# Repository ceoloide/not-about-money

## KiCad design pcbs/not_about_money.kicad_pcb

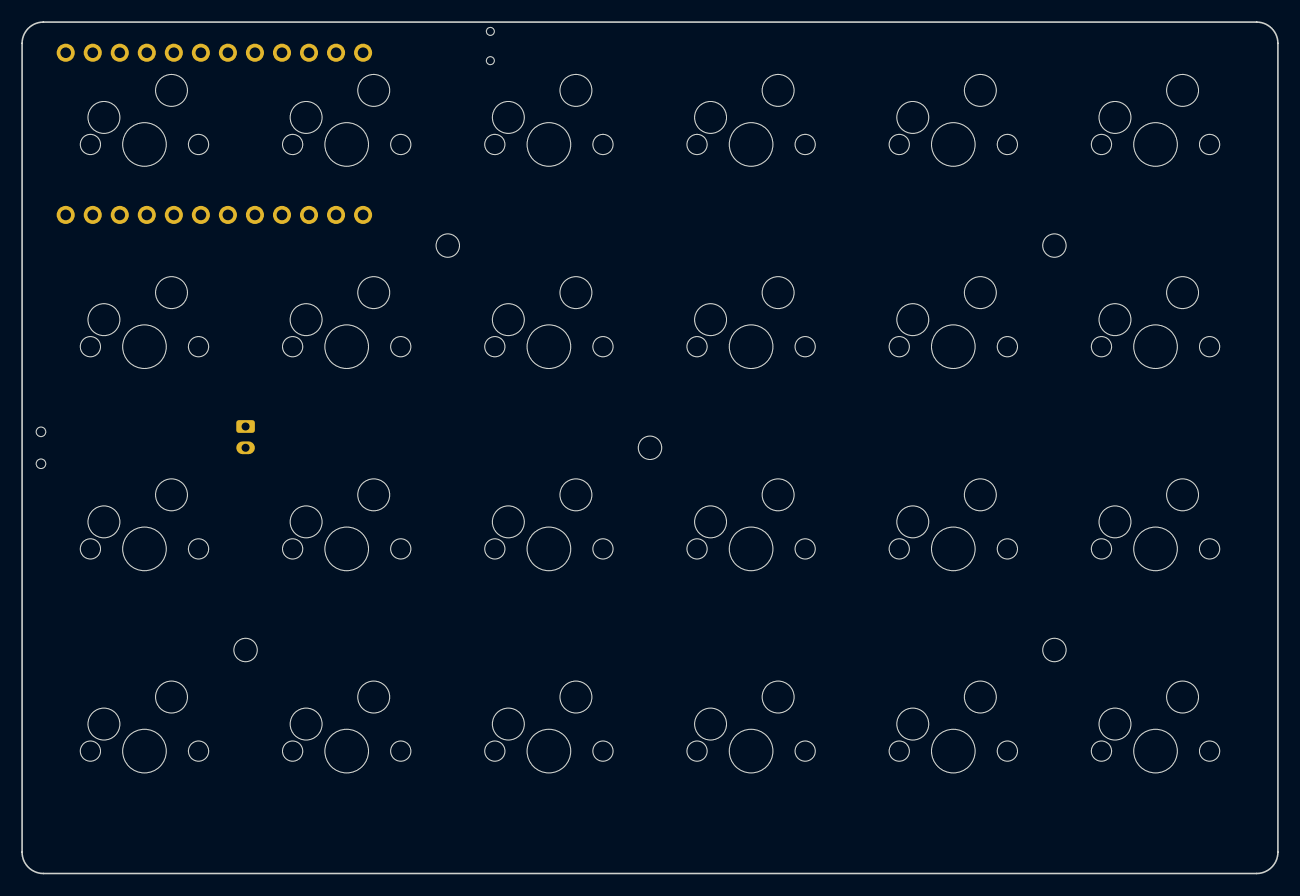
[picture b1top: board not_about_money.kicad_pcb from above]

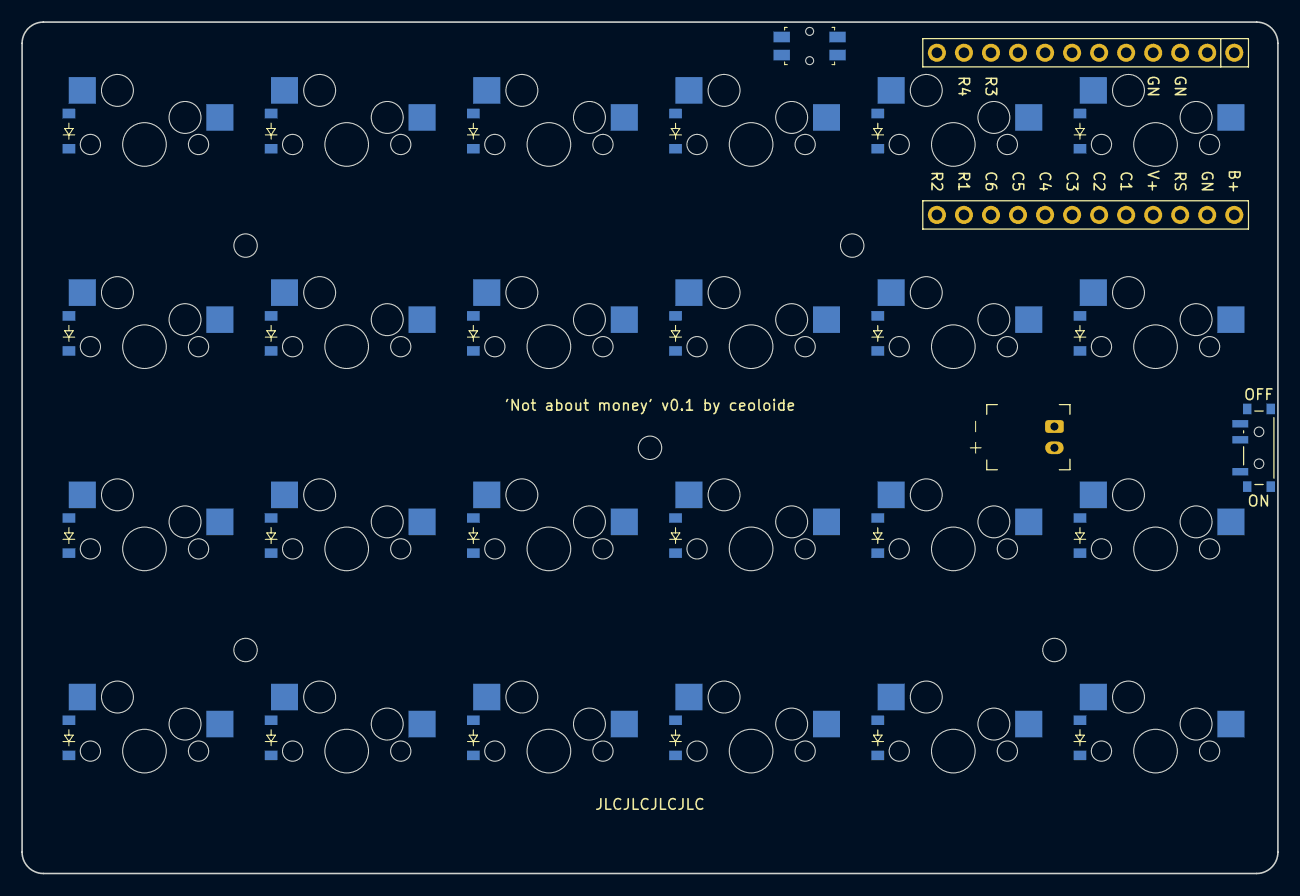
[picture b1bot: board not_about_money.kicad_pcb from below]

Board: 2 copper layers, 118.0 x 80.0 mm, 57 parts (52 on the bottom side), 38 nets, no tracks yet.

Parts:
D1, D2, D3, D4, D5, D6, D7, D8, D9, D10, D11, D12, D13, D14, D15, D16, D17, D18, D19, D20, D21, D22, D23, D24: diode_tht_sod123
JST1: battery_connector_jst_ph_2
MCU1: mcu_nice_nano
MH1, MH2, MH3, MH4, MH5: mounting_hole_npth
PWR1: power_switch_smd_side
RST1: reset_switch_smd_side
S1, S2, S3, S4, S5, S6, S7, S8, S9, S10, S11, S12, S13, S14, S15, S16, S17, S18, S19, S20, S21, S22, S23, S24: switch_mx

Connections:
BAT_P: JST1.2, PWR1.1
C1: MCU1.20, S1.1, S2.1, S3.1, S4.1
C2: MCU1.19, S5.1, S6.1, S7.1, S8.1
C3: MCU1.18, S9.1, S10.1, S11.1, S12.1
C4: MCU1.17, S13.1, S14.1, S15.1, S16.1
C5: MCU1.16, S17.1, S18.1, S19.1, S20.1
C6: MCU1.15, S21.1, S22.1, S23.1, S24.1
GND: JST1.1, MCU1.3, MCU1.4, MCU1.23, RST1.1, RST1.3
R1: D4.1, D8.1, D12.1, D16.1, D20.1, D24.1, MCU1.14
R2: D3.1, D7.1, D11.1, D15.1, D19.1, D23.1, MCU1.13
R3: D2.1, D6.1, D10.1, D14.1, D18.1, D22.1, MCU1.10
R4: D1.1, D5.1, D9.1, D13.1, D17.1, D21.1, MCU1.11
RAW: MCU1.24, PWR1.2
RST: MCU1.22, RST1.2, RST1.4
c1_r1: D4.2, S4.2
c1_r2: D3.2, S3.2
c1_r3: D2.2, S2.2
c1_r4: D1.2, S1.2
c2_r1: D8.2, S8.2
c2_r2: D7.2, S7.2
c2_r3: D6.2, S6.2
c2_r4: D5.2, S5.2
c3_r1: D12.2, S12.2
c3_r2: D11.2, S11.2
c3_r3: D10.2, S10.2
c3_r4: D9.2, S9.2
c4_r1: D16.2, S16.2
c4_r2: D15.2, S15.2
c4_r3: D14.2, S14.2
c4_r4: D13.2, S13.2
c5_r1: D20.2, S20.2
c5_r2: D19.2, S19.2
c5_r3: D18.2, S18.2
c5_r4: D17.2, S17.2
c6_r1: D24.2, S24.2
c6_r2: D23.2, S23.2
c6_r3: D22.2, S22.2
c6_r4: D21.2, S21.2

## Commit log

2024-11-11 Update build.sh to use latest Freerouting SNAPSHOT
2024-11-11 Add .gitignore
2024-11-11 Change main PCB name
2024-11-11 Remove unused build files
2024-11-11 Remove unneccessary files
2024-11-11 Remove JSCAD build
2024-11-11 Update board config with final footprint positions
2024-11-11 Update build scripts to the new board name
2024-11-11 Fix board anchor shift
2024-11-11 Update Dockerfile with latest Freerouting snapshot
2024-11-11 Update outputs
2024-11-11 Add GitHub Action workflow
2024-11-11 Fixed reference to a different board
2024-11-11 Update assets
2024-11-11 Move the rest button slightly
2024-11-11 Add board outline DFX
2024-11-11 Update Dockerfile
2024-11-11 Fix wrong Freerouting URL
2024-11-11 Update the build.sh file to make use of new Docker image
2024-11-11 Update MCU labels and pin assignments
2024-11-11 Update footprints library to fix MCU silkscreen
2024-11-11 Remove assets in the wrong location
2024-11-12 Update build scripts
2024-11-12 Update footprints library to fix MX switch pads
2024-11-12 Switch to HTTPS submodule for GitHub Codespaces compatibility
2024-11-12 Move output to the repository root for ease of discovery
2024-11-12 Add skeleton 3D printed case configuration for testing
2024-11-12 Update GitHub Action workflow with correct folder structure
2024-11-12 Fix build script
2024-11-12 Fix the output paths to persist
2024-11-14 Fix wrong URL for Freerouting 2.0.1
2024-11-14 Add basic top case configuration
2024-11-14 Update license
2024-11-14 Update references to Docker image
2024-11-14 Move Dockerfile to its own repository (ceoloide/ergogen-freerouting)
2024-11-14 Fix missing debug flag and related assets
2024-11-14 Update kibot settings
